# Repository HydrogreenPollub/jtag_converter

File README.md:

View this project on [CADLAB.io](https://cadlab.io/project/29270). 

# jtag_converter
 Git

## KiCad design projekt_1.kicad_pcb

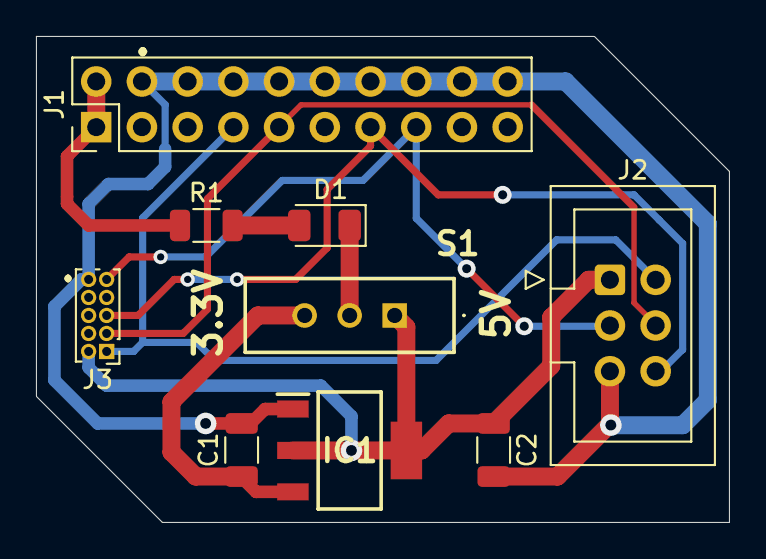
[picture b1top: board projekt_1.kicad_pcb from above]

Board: 2 copper layers, 38.5 x 27.0 mm, 9 parts (0 on the bottom side), 10 nets.

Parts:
C1, C2: 1uF; C_1206_3216Metric
D1: LED; LED_1206_3216Metric
IC1: LDO_Module; SOT230P700X180-4N
J1: C_02x10; PinHeader_2x10_P2.54mm_Vertical
J2: C_02x03; IDC-Header_2x03_P2.54mm_Vertical
J3: C_02x05; PinHeader_2x05_P1.00mm_Vertical
R1: 300; R_1206_3216Metric
S1: Switch_1; SLW1166415ASD

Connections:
/RESET: J1.15, J2.3, J3.9
/SWCLK: J1.9, J2.4, J3.3
/SWDIO: J1.7, J2.2, J3.1
/SWO: J1.13, J2.6, J3.5
/VCC: J1.1, J1.2, R1.1
/VCC_2: C2.1, IC1.2 (OUT_1), IC1.4 (OUT_2), J2.1, J3.2, S1.1 (NC)
GND: C1.2, C2.2, IC1.1 (GND), J1.4, J1.6, J1.8, J1.10, J1.12, J1.14, J1.16, J1.18, J1.20, J2.5, J3.10
unnamed: D1.2 (A), R1.2
unnamed: D1.1 (K), S1.2 (COM)
unnamed: C1.1, IC1.3 (INPUT), S1.3 (NO)

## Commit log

2025-04-18 Add files
    Git
2025-04-18 Backlink to CADLAB.io has been added.
